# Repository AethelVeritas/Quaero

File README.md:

# Quaero
*"quaero" - Latin verb meaning "I seek", "I am looking"*  
As the name suggests, this is a keyboard designed to help the daily 'seeking' through the internet, making typing more efficient and comfortable.  
  
# Key Features
- Uses low-profile affordable Gateron KS-33 switches  
- PCB is compatible with an OLED and Cirque touchpad (with an I2C adapter)  
- Removable number row  
- Ergonomic splay and thumb clusters  
- Hotswappable
  
# Gallery 

# License
Quaero is licensed under CERN-OHL-P-2.0.

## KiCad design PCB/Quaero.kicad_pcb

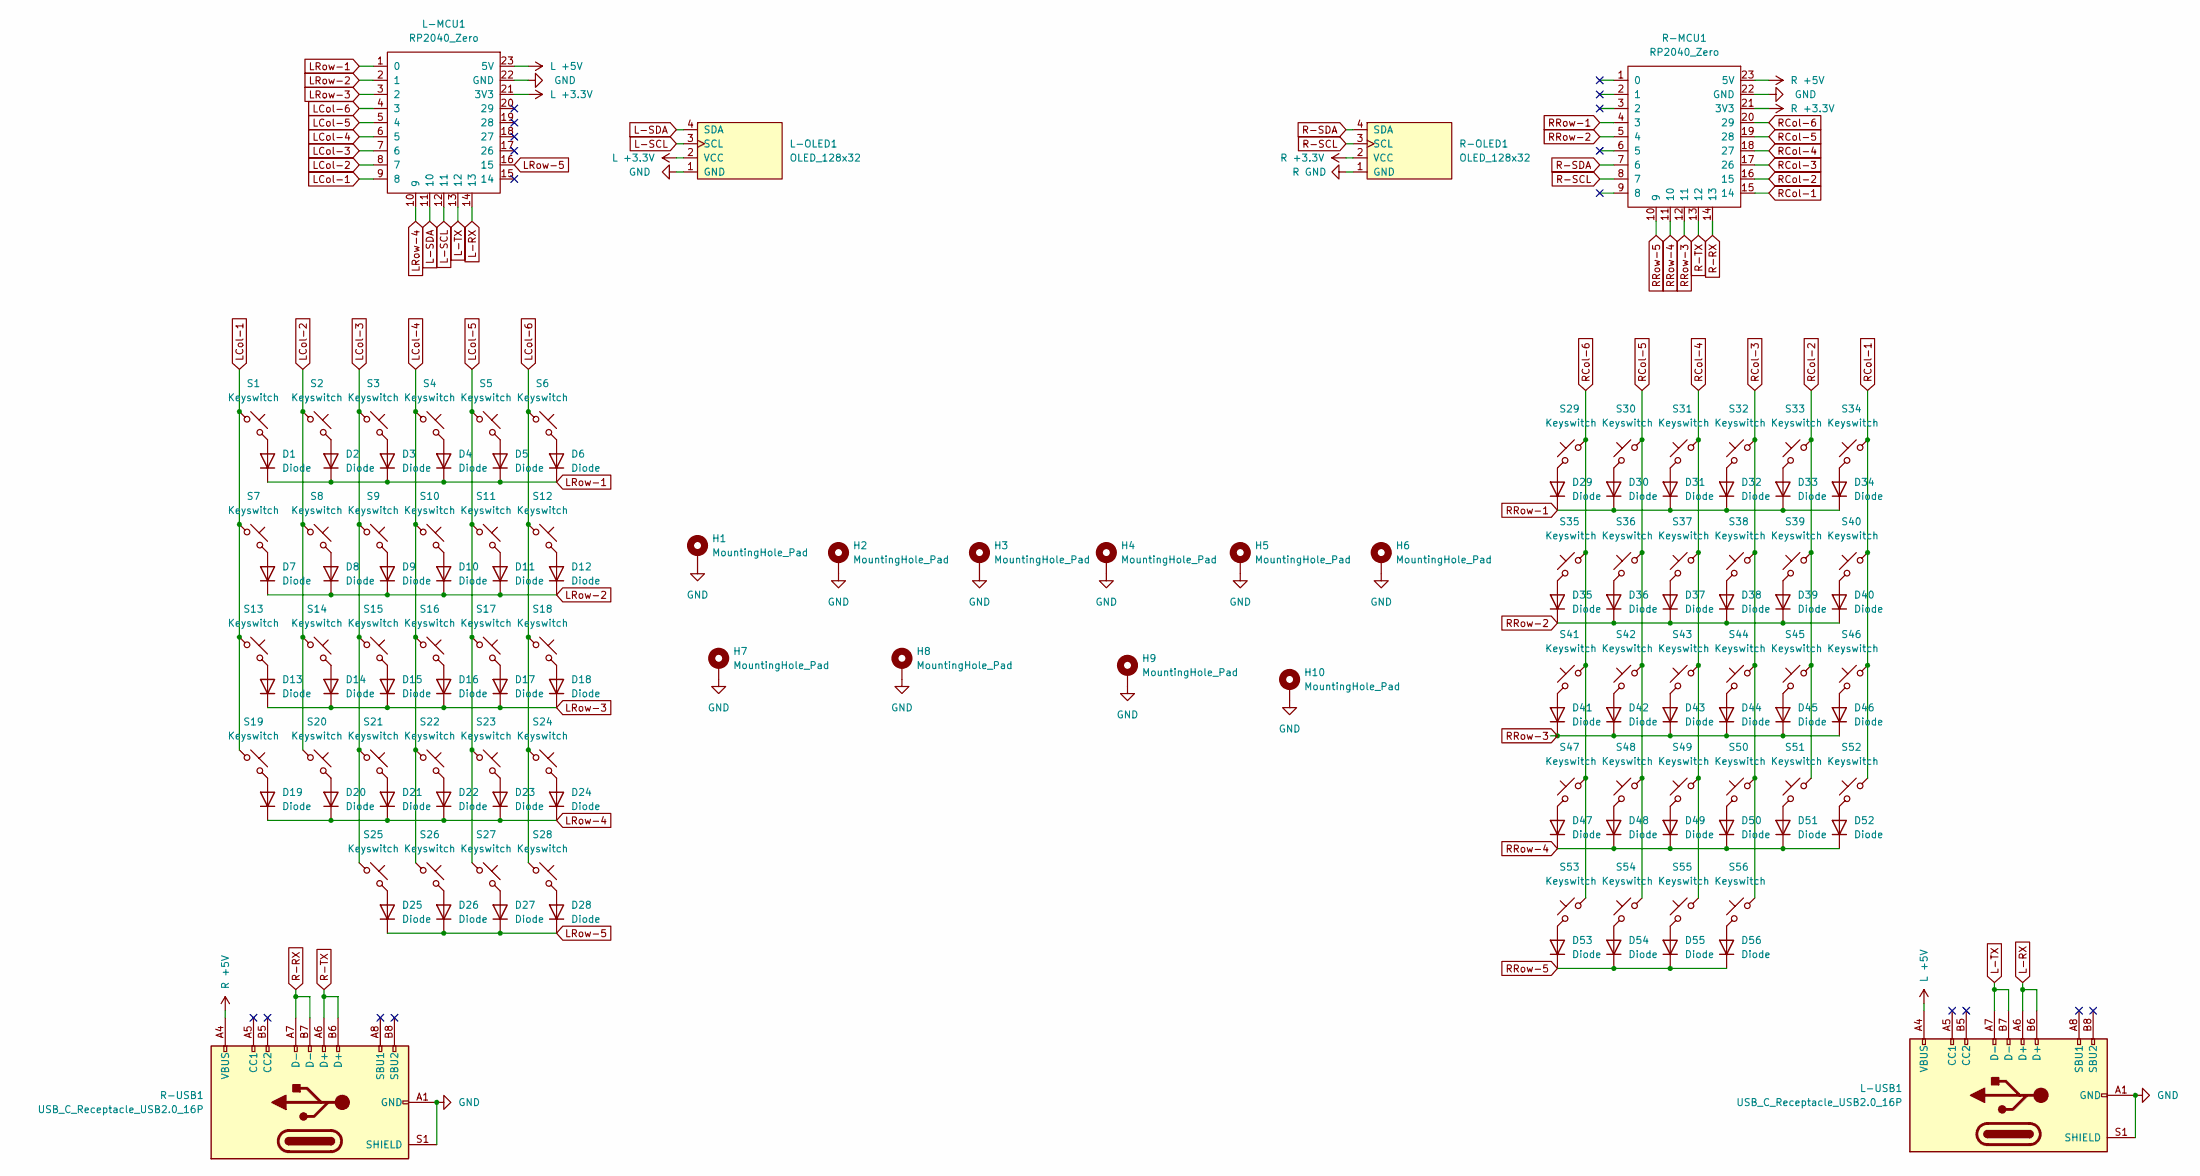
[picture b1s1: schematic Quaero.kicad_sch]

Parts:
D1, D2, D3, D4, D5, D6, D7, D8, D9, D10, D11, D12, D13, D14, D15, D16, D17, D18, D19, D20, D21, D22, D23, D24, D25, D26, D27, D28: Diode; D_DO-35_SOD27_P7.62mm_Horizontal
D29, D30, D31, D32, D33, D34, D35, D36, D37, D38, D39, D40, D41, D42, D43, D44, D45, D46, D47, D48, D49, D50, D51, D52, D53, D54, D55, D56: Diode
H1, H2, H3, H4, H5, H6, H7, H8, H9, H10: MountingHole_Pad; MountingHole_2.2mm_M2_Pad
L-MCU1: RP2040_Zero; RP2040_Zero_Flipped
L-OLED1: OLED_128x32
L-USB1: USB_C_Receptacle_USB2.0_16P; USB_C_Receptacle_GCT_USB4085
R-MCU1: RP2040_Zero; RP2040_Zero_Flipped
R-OLED1: OLED_128x32
R-USB1: USB_C_Receptacle_USB2.0_16P; USB_C_Receptacle_GCT_USB4085
S1, S2, S3, S4, S5, S6, S7, S8, S9, S10, S11, S12, S13, S14, S15, S16, S17, S18, S19, S20, S21, S22, S23, S24, S25, S26, S27, S28, S29, S30, S31, S32, S33, S34, S35, S36, S37, S38, S39, S40, S41, S42, S43, S44, S45, S46, S47, S48, S49, S50, S51, S52, S53, S54, S55, S56: Keyswitch

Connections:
GND: H1.1, H2.1, H3.1, H4.1, H5.1, H6.1, H7.1, H8.1, H9.1, H10.1, L-MCU1.22 (GND), L-OLED1.1 (GND), L-USB1.A1 (GND), L-USB1.A12 (GND), L-USB1.B1 (GND), L-USB1.B12 (GND), L-USB1.S1 (SHIELD), R-MCU1.22 (GND), R-USB1.A1 (GND), R-USB1.A12 (GND), R-USB1.B1 (GND), R-USB1.B12 (GND), R-USB1.S1 (SHIELD); also elsewhere on the board
L +3.3V: L-MCU1.21 (3V3), L-OLED1.2 (VCC)
L +5V: L-MCU1.23 (5V), L-USB1.A4 (VBUS), L-USB1.A9 (VBUS), L-USB1.B4 (VBUS), L-USB1.B9 (VBUS)
L-RX: L-MCU1.14 (13), L-USB1.A6 (D+), L-USB1.B6 (D+)
L-SCL: L-MCU1.12 (11), L-OLED1.3 (SCL)
L-SDA: L-MCU1.11 (10), L-OLED1.4 (SDA)
L-TX: L-MCU1.13 (12), L-USB1.A7 (D-), L-USB1.B7 (D-)
LCol-1: L-MCU1.9 (8), S1.1, S7.1, S13.1, S19.1
LCol-2: L-MCU1.8 (7), S2.1, S8.1, S14.1, S20.1
LCol-3: L-MCU1.7 (6), S3.1, S9.1, S15.1, S21.1, S25.1
LCol-4: L-MCU1.6 (5), S4.1, S10.1, S16.1, S22.1, S26.1
LCol-5: L-MCU1.5 (4), S5.1, S11.1, S17.1, S23.1, S27.1
LCol-6: L-MCU1.4 (3), S6.1, S12.1, S18.1, S24.1, S28.1
LRow-1: D1.1 (K), D2.1 (K), D3.1 (K), D4.1 (K), D5.1 (K), D6.1 (K), L-MCU1.1 (0)
LRow-2: D7.1 (K), D8.1 (K), D9.1 (K), D10.1 (K), D11.1 (K), D12.1 (K), L-MCU1.2 (1)
LRow-3: D13.1 (K), D14.1 (K), D15.1 (K), D16.1 (K), D17.1 (K), D18.1 (K), L-MCU1.3 (2)
LRow-4: D19.1 (K), D20.1 (K), D21.1 (K), D22.1 (K), D23.1 (K), D24.1 (K), L-MCU1.10 (9)
LRow-5: D25.1 (K), D26.1 (K), D27.1 (K), D28.1 (K), L-MCU1.16 (15)
unnamed: D1.2 (A), S1.2
unnamed: D2.2 (A), S2.2
unnamed: D3.2 (A), S3.2
unnamed: D4.2 (A), S4.2
unnamed: D5.2 (A), S5.2
unnamed: D6.2 (A), S6.2
unnamed: D7.2 (A), S7.2
unnamed: D8.2 (A), S8.2
unnamed: D9.2 (A), S9.2
unnamed: D10.2 (A), S10.2
unnamed: D11.2 (A), S11.2
unnamed: D12.2 (A), S12.2
unnamed: D13.2 (A), S13.2
unnamed: D14.2 (A), S14.2
unnamed: D15.2 (A), S15.2
unnamed: D16.2 (A), S16.2
unnamed: D17.2 (A), S17.2
unnamed: D18.2 (A), S18.2
unnamed: D19.2 (A), S19.2
unnamed: D20.2 (A), S20.2
unnamed: D21.2 (A), S21.2
unnamed: D22.2 (A), S22.2
unnamed: D23.2 (A), S23.2
unnamed: D24.2 (A), S24.2
unnamed: D25.2 (A), S25.2
unnamed: D26.2 (A), S26.2
unnamed: D27.2 (A), S27.2
unnamed: D28.2 (A), S28.2
unnamed: D29.2 (A), S29.1
unnamed: D30.2 (A), S30.1
unnamed: D31.2 (A), S31.1
unnamed: D32.2 (A), S32.1
unnamed: D33.2 (A), S33.1
unnamed: D34.2 (A), S34.1
unnamed: D35.2 (A), S35.1
unnamed: D36.2 (A), S36.1
unnamed: D37.2 (A), S37.1
unnamed: D38.2 (A), S38.1
unnamed: D39.2 (A), S39.1
unnamed: D40.2 (A), S40.1
unnamed: D41.2 (A), S41.1
unnamed: D42.2 (A), S42.1
unnamed: D43.2 (A), S43.1
unnamed: D44.2 (A), S44.1
unnamed: D45.2 (A), S45.1
unnamed: D46.2 (A), S46.1
unnamed: D47.2 (A), S47.1
unnamed: D48.2 (A), S48.1
unnamed: D49.2 (A), S49.1
unnamed: D50.2 (A), S50.1
unnamed: D51.2 (A), S51.1
unnamed: D52.2 (A), S52.1
unnamed: D53.2 (A), S53.1
unnamed: D54.2 (A), S54.1
unnamed: D55.2 (A), S55.1
unnamed: D56.2 (A), S56.1
R +3.3V: R-MCU1.21 (3V3), R-OLED1.2 (VCC)
R +5V: R-MCU1.23 (5V), R-USB1.A4 (VBUS), R-USB1.A9 (VBUS), R-USB1.B4 (VBUS), R-USB1.B9 (VBUS)
R GND: R-OLED1.1 (GND)
R-RX: R-MCU1.14 (13), R-USB1.A7 (D-), R-USB1.B7 (D-)
R-SCL: R-MCU1.8 (7), R-OLED1.3 (SCL)
R-SDA: R-MCU1.7 (6), R-OLED1.4 (SDA)
R-TX: R-MCU1.13 (12), R-USB1.A6 (D+), R-USB1.B6 (D+)
RCol-1: R-MCU1.15 (14), S34.2, S40.2, S46.2, S52.2
RCol-2: R-MCU1.16 (15), S33.2, S39.2, S45.2, S51.2
RCol-3: R-MCU1.17 (26), S32.2, S38.2, S44.2, S50.2, S56.2
RCol-4: R-MCU1.18 (27), S31.2, S37.2, S43.2, S49.2, S55.2
RCol-5: R-MCU1.19 (28), S30.2, S36.2, S42.2, S48.2, S54.2
RCol-6: R-MCU1.20 (29), S29.2, S35.2, S41.2, S47.2, S53.2
RRow-1: D29.1 (K), D30.1 (K), D31.1 (K), D32.1 (K), D33.1 (K), D34.1 (K), R-MCU1.4 (3)
RRow-2: D35.1 (K), D36.1 (K), D37.1 (K), D38.1 (K), D39.1 (K), D40.1 (K), R-MCU1.5 (4)
RRow-3: D41.1 (K), D42.1 (K), D43.1 (K), D44.1 (K), D45.1 (K), D46.1 (K), R-MCU1.12 (11)
RRow-4: D47.1 (K), D48.1 (K), D49.1 (K), D50.1 (K), D51.1 (K), D52.1 (K), R-MCU1.11 (10)
RRow-5: D53.1 (K), D54.1 (K), D55.1 (K), D56.1 (K), R-MCU1.10 (9)

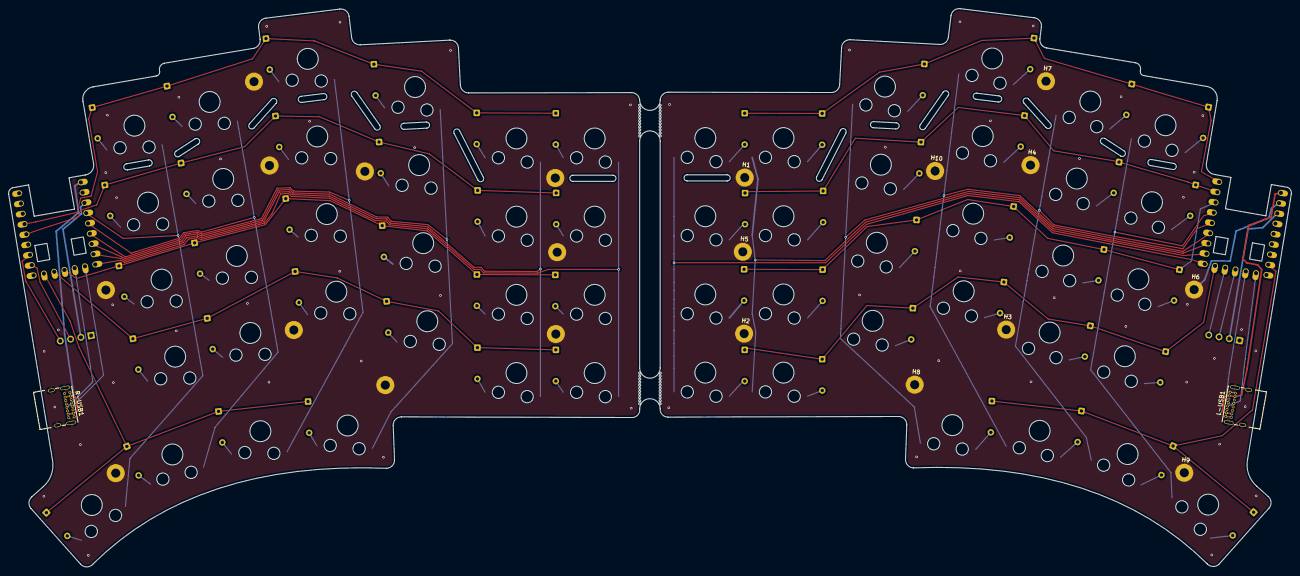
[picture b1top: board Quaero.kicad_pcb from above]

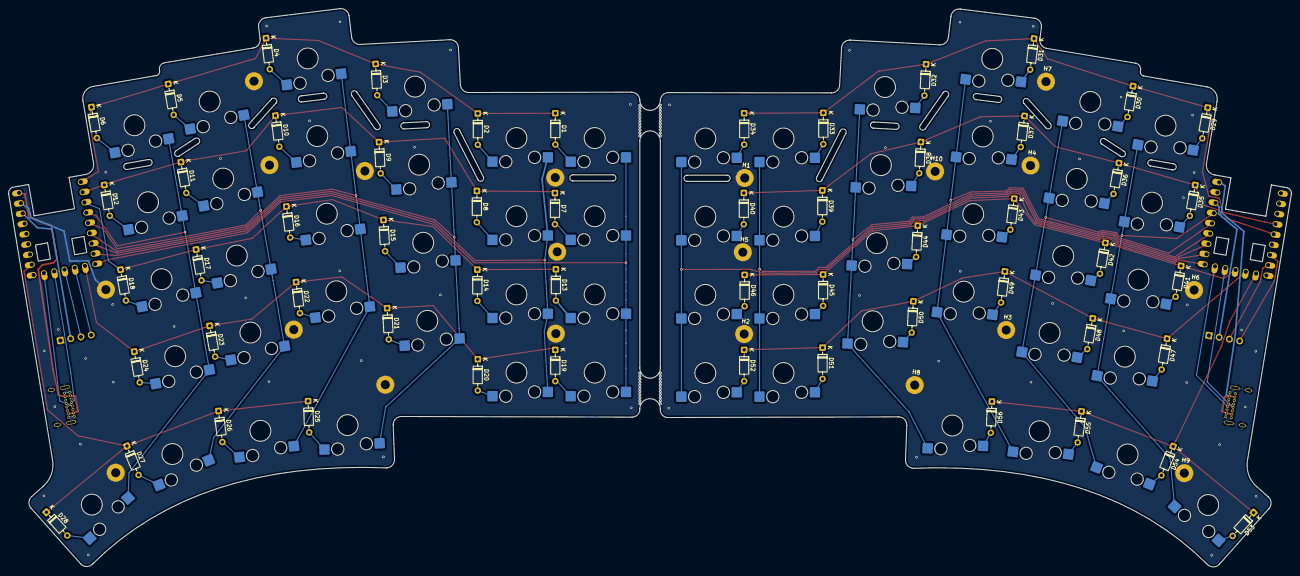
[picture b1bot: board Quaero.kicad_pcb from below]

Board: 2 copper layers, 312.5 x 136.0 mm, 140 parts (122 on the bottom side), 91 nets.

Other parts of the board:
H1#2, H2#2, H3#2, H4#2, H5#2, H6#2, H7#2, H8#2, H9#2, H10#2: MountingHole_Pad; MountingHole_2.2mm_M2_Pad
mouse-bite-5mm-slot, mouse-bite-5mm-slot#2: VAL**; mouse-bite-5mm-slot

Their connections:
GND: H1#2.1, H2#2.1, H3#2.1, H4#2.1, H5#2.1, H6#2.1, H7#2.1, H8#2.1, H9#2.1, H10#2.1; also elsewhere on the board

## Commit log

2025-07-01 Update JOURNAL.md (Retro Journaling)
2025-07-05 Left Side Routing Attempt 2
2025-07-05 Added files to PCB folder
2025-07-07 Removed unnecessary .kicad files from the root folder
2025-07-20 Left side routing attempt 4, added pics folder
2025-07-20 Left side partial routing attempt 4
2025-07-20 Testing pic preview in JOURNAL.md
2025-07-20 Testing pic preview in JOURNAL.md, try 2
2025-07-20 Testing pic preview in JOURNAL.md, try 3
2025-07-24 Updated to RP2040, routing columns attempt 1
2025-07-24 Revised routing, changed the MCU to the RP2040 Zero, changed the USB-C schematic
2025-07-25 Added picture files for last journal entry
2025-07-27 Updated Journal
2025-07-27 Safety commit before flipping rp2040
2025-07-31 Finished right side
2025-07-31 added pics
2025-07-31 Fixed pics not showing up in JOURNAL.md
2025-08-27 Final PCB
2025-08-27 Upated JOURNAL.md
2026-02-17 added files + readme improvements
2026-02-17 small readme changes, added license
